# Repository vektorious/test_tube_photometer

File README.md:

<p align="center">

<h1 align="center">Test Tube Photometer <br>
Flow-through Photometer
</h1>
<h3 align="center">Low-cost hardware setup for measuring light extinction and optical densities</h3>
</p>
<br>

## Welcome!

You can find a description on how to build the OLD VERSION of the photometer [here](https://alexanderkutschera.com/research/photometer-shopping-list.html).

- [What's this all about?](#background)
- [How can I build my own photometer?](#building-instructions)
- [How can I contribute?](#contributing)
- [Wait, why should I contribute?](#report-issues)
- [Who is behind all this?](#who-is-behind-all-this)

### Background

This photometer can be used for science. We published a paper about it in [Current Microbiology](https://link.springer.com/article/10.1007/s00284-017-1370-3). (Yes, the journal has a paywall. It maybe was not the right decision to publish it there but I'm trying to make up for it by providing all info here in the repository. If you want the paper I can send it to you. Just drop me an [email](mailto:alexander.kutschera@gmail.com).)

#### What's a photometer?
Photometers are used to measure light extinction in liquids to analyse their content. They basically shine light through a certain amount of the liquid from one side and measure the light that's left on the other side. Among other things, photometers are used to measure the densities of bacterial cultures on a regular basis. You can determine them by comparing photometer measurements of culture media with (sample value) and without bacteria (blank value). Using physical laws you can then calculate the optical density of your sample.

#### Why a test tube photometer?
Well, I'm a lazy person. In order to measure the optical density of my bacterial cultures I always had to take a sample from them. This usually meant I had to work sterile to avoid contamination of my cultures which is a bit time consuming. That's why I asked myself if there is a way to measure the density directly in the test tube without having to open it. There are already some test tube photometer out there but they are expensive and often require the use of specific test tubes. That's why I started to develop a photometer which I could use with the standard test tubes.

<p align="center">

#### And why a flow-through photometer?
With a flow-through photometer can be used to monitor light extinction in any liquid independent of the container. The sample is constantly pumped through the photometer and OD is measured over time. I started to work on a flow-through version of the test tube photometer as part of a [Biomaker](https://www.biomaker.org/) project. We were developing an [low-cost microbial bioreactor](https://www.hackster.io/open-bioeconomy-lab/microbial-bioreactor-d7f61b) and I was looking into ways to measure the culture density in the device over time. But you can also use it for example to measure culture densities in a beaker or monitor the turbidity of river water.

<p align="center">

### Assembly instructions

The photometer is designed to be modular. You can add as many measurement cells as you like (well ok. you are limited by the amounts of analog inputs your microcontroller has).

There are two was of building the photometer:

#### 1. Using a breadboard and cables

**Advantage:**
You don't need many special parts apart from the sensor (opt101). Some cables, resistors and a breadboard are required as well.

**Disadvantage:**
The connections are not very stable which could produce reading errors. Wiring the opt101 just with cable is a bit confusing (at least it was for me). Apart from that, the legs of the sensor break easily if you bend them to often and too much.

#### 2. Using PCBs (Arduino Nano HAT and the sensor PCB)

**Advantage:**
All the electronics are easy to put together. The connections are stable and secure. You can quickly add connect more measurement cells.

**Disadvantage:**
Well.. you need the PCBs. But you can easily order them from a PCB manufacturer with the gerber files in this repository. You'll find more info about this in [/hardware/pcb/README.md](https://github.com/vektorious/test_tube_photometer/tree/master/hardware/pcb).

Both ways of building the photometer are described [in the instructions folder](https://github.com/vektorious/test_tube_photometer/tree/master/instructions).

### Contributing

This is a side project of mine and it is not actively developed. I work on it sometimes and try to improve the design and fix errors. I try to do my best to document it as good as possible so anybody can copy this and build their own photometer. You are welcome to contribute to the project by adding more designs for the housing and improving the building instructions.

### Report issues

Notice a mistake or errors? Please file any bugs, requests, or questions in the [issue tracker](https://github.com/vektorious/test_tube_photometer/issues)!

If you are new to GitHub issue tracker take a look [here](https://guides.github.com/features/issues/).

### Who is behind all this?

Please contact me if you have any questions.

<p align="center">
 </br>This work is licensed under a <a rel="license" href="http://creativecommons.org/licenses/by-sa/4.0/">Creative Commons Attribution-ShareAlike 4.0 International License</a>.
</p>

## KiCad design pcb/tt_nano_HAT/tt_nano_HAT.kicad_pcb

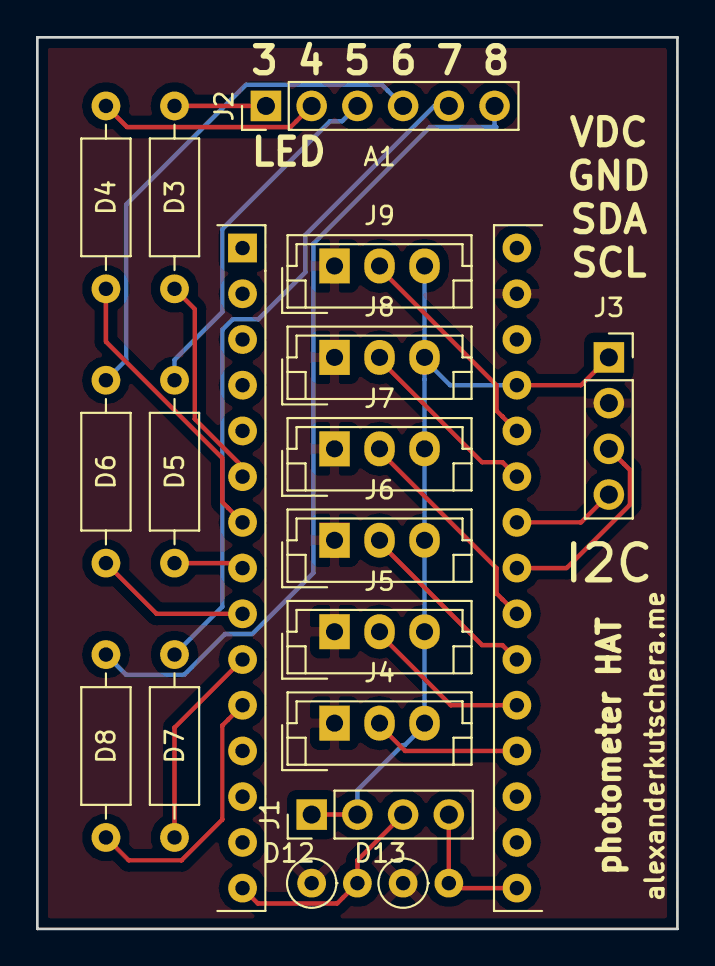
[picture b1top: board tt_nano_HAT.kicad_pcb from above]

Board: 2 copper layers, 35.6 x 49.5 mm, 18 parts (0 on the bottom side), 24 nets.

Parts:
A1: Arduino_Nano_v3.x; Arduino_Nano2
D3, D4, D5, D6, D7, D8: R; R_Axial_DIN0207_L6.3mm_D2.5mm_P10.16mm_Horizontal
D12, D13: R; R_Axial_DIN0207_L6.3mm_D2.5mm_P2.54mm_Vertical
J1: Conn_01x04_Male; PinHeader_1x04_P2.54mm_Vertical
J2: Conn_01x06_Male; PinHeader_1x06_P2.54mm_Vertical
J3: Conn_01x04_Female; PinSocket_1x04_P2.54mm_Vertical
J4, J5, J6, J7, J8, J9: Conn_01x03_Male; JST_EH_B03B-EH-A_1x03_P2.50mm_Vertical

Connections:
unnamed: A1.6, D3.1
unnamed: A1.7, D4.1
unnamed: A1.8, D5.1
unnamed: A1.9, D6.1
unnamed: A1.10, D7.1
unnamed: A1.11, D8.1
unnamed: A1.15, D12.2, J1.3
unnamed: A1.16, D13.2, J1.4
unnamed: A1.19, J4.2
unnamed: A1.20, J5.2
unnamed: A1.21, J6.2
unnamed: A1.22, J7.2
unnamed: A1.23, J3.3
unnamed: A1.24, J3.4
unnamed: A1.25, J8.2
unnamed: A1.26, J9.2
unnamed: A1.27, J1.1, J1.2, J3.1, J4.3, J5.3, J6.3, J7.3, J8.3, J9.3
unnamed: A1.29, D12.1, D13.1, J3.2, J4.1, J5.1, J6.1, J7.1, J8.1, J9.1
unnamed: D3.2, J2.1
unnamed: D4.2, J2.2
unnamed: D5.2, J2.3
unnamed: D6.2, J2.4
unnamed: D7.2, J2.5
unnamed: D8.2, J2.6

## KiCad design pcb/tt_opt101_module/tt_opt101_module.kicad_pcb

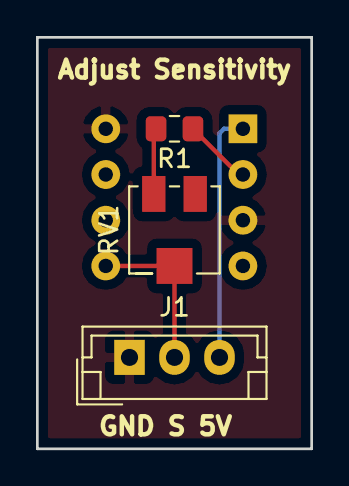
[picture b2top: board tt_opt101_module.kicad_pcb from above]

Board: 2 copper layers, 15.2 x 22.9 mm, 4 parts (1 on the bottom side), 5 nets.

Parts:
J1: Conn_01x03_Male; JST_EH_B03B-EH-A_1x03_P2.50mm_Vertical
O1: opt101; DIP-8_W7.62mm
R1: R; R_0805_2012Metric_Pad1.15x1.40mm_HandSolder
RV1: R_POT; Potentiometer_Bourns_3214J_Horizontal

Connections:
+5V: J1.3, O1.1
GND: J1.1, O1.3, O1.8
unnamed: J1.2, O1.5, RV1.2
unnamed: O1.2, R1.1
unnamed: R1.2, RV1.1

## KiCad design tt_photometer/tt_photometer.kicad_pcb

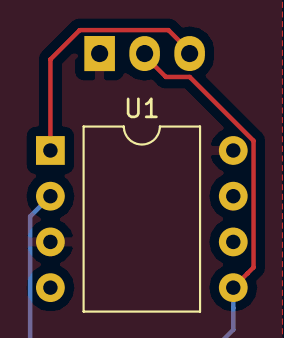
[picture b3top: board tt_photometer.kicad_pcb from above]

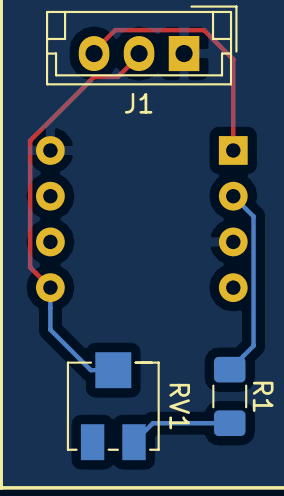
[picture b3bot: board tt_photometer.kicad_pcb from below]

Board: 2 copper layers, 4 parts (3 on the bottom side), 5 nets.

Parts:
J1: Conn_01x03_Male; JST_EH_B03B-EH-A_1x03_P2.50mm_Vertical
R1: R; R_1206_3216Metric_Pad1.42x1.75mm_HandSolder
RV1: R_POT; Potentiometer_Bourns_3214J_Horizontal
U1: opt101; DIP-8_W10.16mm

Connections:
+5V: J1.3, U1.1
GND: J1.1, U1.3, U1.8
unnamed: J1.2, RV1.2, U1.5
unnamed: R1.1, U1.2
unnamed: R1.2, RV1.1

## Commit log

2017-12-09 FirstCommit
2017-12-09 pics_upload
2017-12-09 upload sketch
2017-12-09 sketch_update
2017-12-09 new pic
2017-12-09 sketch
2017-12-12 added_.scad_files
2017-12-14 new files
2017-12-14 corrections
2018-10-06 added kitcad
2018-12-04 Created PCBs
2019-03-20 Updated PCB and 3D files
2019-03-20 reorganized repo
2019-03-21 Included BOM
2019-03-25 uploaded new .stl and BOM
2019-03-26 Fixed Errors in README
2019-05-30 update pcb
2019-06-10 uploaded cuvette cell stls
2019-06-14 updated stls
2019-06-23 uploaded flow_through files
2019-08-23 Updated flow-through housing
2019-11-16 create OKH manifest to test tube photometer
2020-08-03 upload
2020-08-03 rework of repo
2020-08-23 added pics to README
2020-08-23 fixed the image sizes
2020-08-23 updated READMEs
2020-08-30 updated script (more comments!)
2021-07-16 Add kitspace.yml
2021-07-16 Add links to pcb readme
2021-07-16 Fix link to hardware/pcb readme
2022-02-14 Various OKH fixes
    * YAML syntax fixes
    * use BCP 47 compliant language identifiers
    * prefer repo-local path over URL to in-repo files
    * use SPDX compliant license identifiers
2022-06-17 Use actual image in okh yml
2026-05-03 Save local changes before system wipe
